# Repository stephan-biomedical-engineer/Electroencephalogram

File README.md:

# 🧠 Wearable EEG Device – Biomedical Instrumentation I

> A wearable EEG system for real-time brain activity monitoring, designed with embedded systems and IoT principles.

---

## 📚 Project Overview

This project presents a **wearable Electroencephalogram (EEG) device** developed for the **Biomedical Instrumentation I** course. It aims to acquire and process low-amplitude human brain signals (**5µV to 300µV**) across standard EEG frequency bands:

* **Delta (δ):** 0.5 – 4 Hz
* **Theta (θ):** 4 – 8 Hz
* **Alpha (α):** 8 – 13 Hz
* **Beta (β):** 13 – 30 Hz
* **Gamma (γ):** 30 – 100 Hz

This is a full-stack biomedical system, integrating **analog signal conditioning**, **high-resolution digital conversion**, and **wireless data transmission** for real-time EEG visualization.

<p align="center">
  
  <br>
  <b>EEG Hardware Prototype</b>
</p>

<p align="center">
  
  <br>
  <b>Real-Time EEG Interface in Qt</b>
</p>

<p align="center">
  
  <br>
  <b>Physical Setup</b>
</p>

---

## ⚙️ Hardware Architecture

### 🧩 Microcontroller Core

* **STM32H730VBT** SoC
* Features a **16-bit SAR ADC** up to **3.6 MSPS**, ideal for high-resolution EEG data acquisition.

### 🔌 Analog Front-End (AFE)

EEG signals are amplified \~**12000x** and filtered in a 3-stage analog pipeline:

1. **INA333 Instrumentation Amplifier** – 20x gain + initial passive filtering
2. **OPA333 Operational Amplifier** – 600x gain
3. **6th-Order Passive Bandpass Filter** – 0.5 Hz (HP) to 45 Hz (LP)

### 📡 Communication & Storage

* **External Flash:** W25Q512JV QSPI NOR Flash for firmware and logs
* **Wireless Co-Processor:** ESP32-C6-MINI-1H4, communicating via UART

---

## 💾 Firmware Architecture

### STM32H7 Side (Signal Acquisition)

* **DFSDM Peripheral** used for enhanced digital filtering
* **Oversampling & Bit Shifting** increase ADC ENOB
* Implements **Wavelet Transform** for real-time brain wave classification

### ESP32 Side (Wireless Stack)

* Developed using **ESP-IDF** and **FreeRTOS**
* Handles:

  * Serial communication with STM32
  * Data packetization
  * **Wi-Fi communication** to local host
  * **MQTT protocol** for lightweight IoT data streaming

---

## 🧪 Real-Time EEG Visualization

On the host side:

* A **Qt** interface provides live graphical feedback of EEG signals.
* Visualizes brain wave patterns and band activity in real time.

---

## 🛠️ Technologies Used

| Layer            | Tools & Components                         |
| ---------------- | ------------------------------------------ |
| Microcontroller  | STM32H730VBT, STM32CubeIDE                 |
| Analog Circuitry | INA333, OPA333, RC Filters                 |
| Wireless         | ESP32-C6, FreeRTOS (Not yet implemented)   | 
| Protocols        | UART, MQTT, Wi-Fi                          |
| Host Interface   | Qt, C++, HTML5, WebSocket/MQTT |

---

## 🚧 Future Improvements

* ✅ Integrate live FFT for spectral analysis
* ✅ Mobile dashboard version
* 🔲 Dry electrodes support
* 🔲 Artifact rejection (e.g., blink/motion noise)
* 🔲 Bluetooth Low Energy (BLE) alternative

---

## 👨‍🔬 Authors & Acknowledgments
Stephan Costa Barros - 
Electrical Engineering Department – Federal University of Uberlândia (UFU), Brazil

Marcelo Barros de Almeida - 
Electrical Engineering Department – Federal University of Uberlândia (UFU), Brazil

Alcimar Barbosa Soares - 
Electrical Engineering Department – Federal University of Uberlândia (UFU), Brazil

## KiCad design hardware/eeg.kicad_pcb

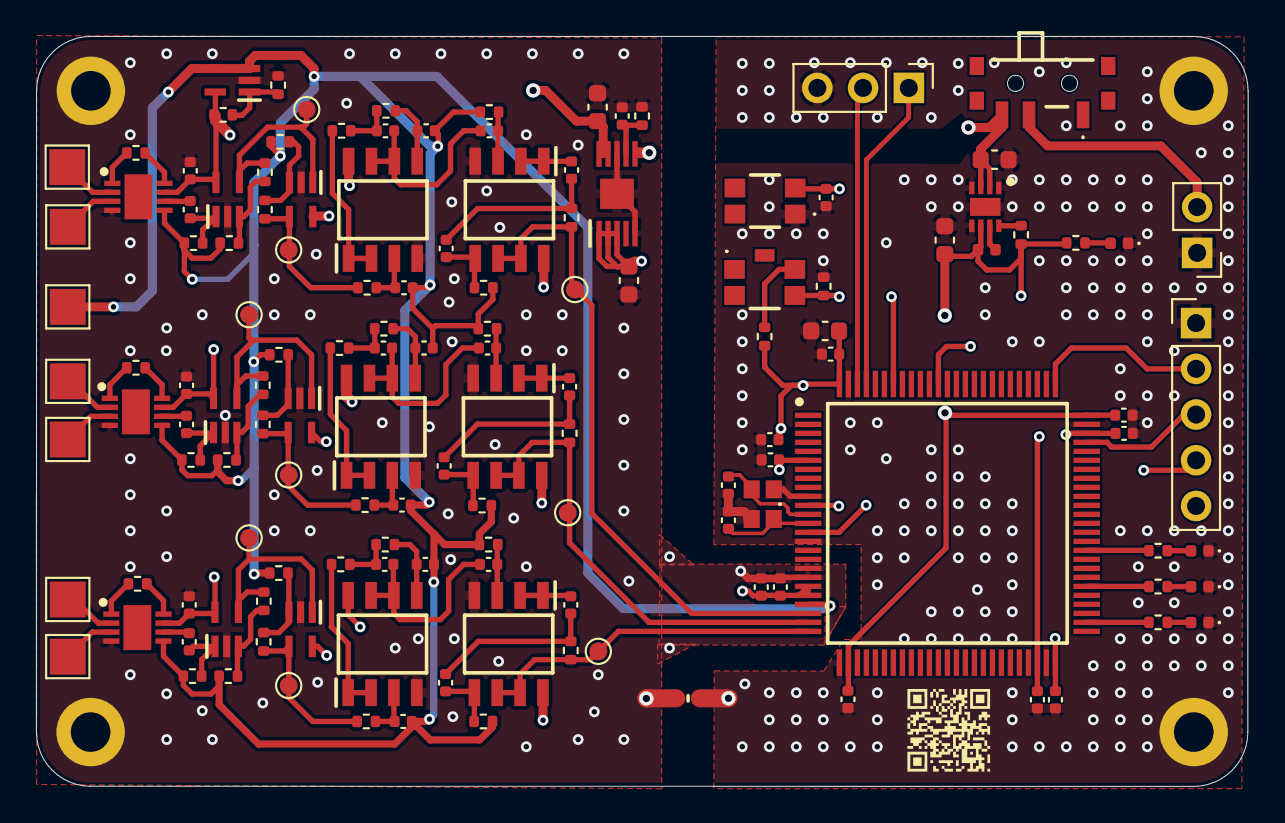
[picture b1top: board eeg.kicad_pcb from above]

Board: 4 copper layers, 67.3 x 41.7 mm, 141 parts (0 on the bottom side), 89 nets.

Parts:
C1, C9, C17, C39: 0.1uF; C_0402_1005Metric
C2, C10, C18: 330nF; C_0402_1005Metric
C3, C5, C11, C13, C19, C21: 36nF; C_0402_1005Metric
C4, C12, C20: 8.2nF; C_0402_1005Metric
C6, C7, C8, C14, C15, C16, C22, C23, C24: 300nF; C_0402_1005Metric
C25, C26, C27, C28, C29, C31, C35: 100nF; C_0402_1005Metric
C30, C40, C42: 4.7uF; C_0603_1608Metric
C32: 1uF; C_0402_1005Metric
C33, C34: 2.2uF; C_0402_1005Metric
C37, C38: 20pF; C_0402_1005Metric
C41: 0.47uF; C_0402_1005Metric
C43: 10uF; C_0603_1608Metric
C44: 22uF; C_0603_1608Metric
CH1+, CH1-, CH2+, CH2-, CH3+, CH3-: TestPoint; TestPoint_Pad_2.0x2.0mm
D1, D2, D3, D4: LED; LED_0402_1005Metric
FB1: FerriteBead_Small; BEADC1005X55N
H1, H2, H3, H4: MountingHole_Pad; MountingHole_2.2mm_M2_DIN965_Pad
IC1: TPS62162QDSGRQ1; SON50P200X200X80-9N
IC2: LT3042IMSE#PBF; SOP50P490X110-11N
IC3: STM32H730VBT6; QFP50P1600X1600X160-100N
IC4: OPA333AIDCKRG4; SOT65P210X110-5N
J1: Battery LiPO; PinHeader_1x02_P2.54mm_Vertical
J2: Conn_01x05; PinHeader_1x05_P2.54mm_Vertical
J4: Serial; PinHeader_1x03_P2.54mm_Vertical
L1: 2.2uH; L_0402_1005Metric
R1, R2: 1M; R_0402_1005Metric
R3, R15, R27: 2.04k; R_0402_1005Metric
R4, R16, R28: 910k; R_0402_1005Metric
R5, R7, R17, R19, R29, R31: 1.5k; R_0402_1005Metric
R6, R8, R18, R20, R30, R32: 750k; R_0402_1005Metric
R9, R21, R33: 97k; R_0402_1005Metric
R10, R22, R34: 149K; R_0402_1005Metric
R11, R23, R35: 276K; R_0402_1005Metric
R12, R24, R36: 967k; R_0402_1005Metric
R13, R25, R37: 1.93M; R_0402_1005Metric
R14, R26, R38: 484k; R_0402_1005Metric
R39, R40, R41, R42, R44: 1k; R_0402_1005Metric
R43: 10k; R_0402_1005Metric
R45: 33.2k; R_0402_1005Metric
R46: 100k; R_0402_1005Metric
REF: TestPoint; TestPoint_Pad_2.0x2.0mm
S1: PCM12SMTBR
SW2: SW_Push_Dual; TL1030AF160BQJ
SW3: SW_Push_Dual; TL1030AF350AQJ
TP1, TP2, TP3, TP4, TP5, TP6, TP7, TP8, TP9: TestPoint; TestPoint_Pad_D1.0mm
U1, U5, U9: INA333xxDRG; SON50P300X300X80-9N-D
U2, U6, U10, U17, U18, U19: OPA333xxDCK; SOT65P210X110-5N
U3, U4, U7, U8, U11, U12: MCP602; SOIC127P600X175-8N
Y1: Crystal_GND24_Small; 830107284409

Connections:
ADC_IN1: IC3.25 (PA3), R14.1, TP3.1, U4.6 (-), U4.7
ADC_IN2: IC3.24 (PA2), R26.1, TP6.1, U8.6 (-), U8.7
ADC_IN3: IC3.23 (PA1), R38.1, TP9.1, U12.6 (-), U12.7
BOOT: IC3.94 (BOOT0), R43.2, SW2.4
EEG_CH1+: CH1+.1, U1.3 (+)
EEG_CH1-: CH1-.1, U1.2 (-)
EEG_CH2+: CH2+.1, U5.3 (+)
EEG_CH2-: CH2-.1, U5.2 (-)
EEG_CH3+: CH3+.1, U9.3 (+)
EEG_CH3-: CH3-.1, U9.2 (-)
GND: C25.2, C26.2, C27.2, C28.2, C29.2, C30.2, C33.2, C34.2, C35.2, C37.2, C38.2, C39.2, C43.2, C44.2, D1.1 (K), D2.1 (K), D3.1 (K), D4.1 (K), FB1.1, H3.1, H4.1, IC1.1 (PGND), IC1.4 (AGND), IC1.5 (FB), IC1.9 (EP), IC3.10 (VSS_1), IC3.15 (PC0), IC3.26 (VSS_2), IC3.49 (VSS_3), IC3.74 (VSS_4), IC3.99 (VSS_5), J1.1, J2.1, J4.3, R43.1, SW3.1, Y1.2, Y1.4
GNDA: C1.1, C9.1, C17.1, C31.2, C32.2, C40.2, C41.2, C42.2, FB1.2, H1.1, H2.1, IC2.5 (ILIM), IC2.8 (GND_1), IC2.11 (GND_2), IC3.18 (PC3_C), IC3.19 (VSSA), IC4.2 (V-), R2.1, R45.2, U1.4 (V-), U2.2 (V-), U3.4 (V-), U4.4 (V-), U5.4 (V-), U6.2 (V-), U7.4 (V-), U8.4 (V-), U9.4 (V-), U10.2 (V-), U11.4 (V-), U12.4 (V-), U17.2 (V-), U18.2 (V-), U19.2 (V-)
HSE_I: C37.1, IC3.12 (PH0-OSC_IN), Y1.1
HSE_O: C38.1, IC3.13 (PH1-OSC_OUT), Y1.3
LED_1: IC3.60 (PD13), R39.1
LED_2: IC3.56 (PD9), R40.1
LED_3: IC3.52 (PB13), R41.1
MCU_RX: IC3.97 (PE0), J4.1
MCU_TX: IC3.98 (PE1), J4.2
unnamed: C2.1, U1.6
unnamed: C5.1, R10.1, R11.1
unnamed: C7.1, C8.2, R14.2
unnamed: C10.1, U5.6
unnamed: C13.1, R22.1, R23.1
unnamed: C15.1, C16.2, R26.2
unnamed: C18.1, U9.6
unnamed: C21.1, R34.1, R35.1
unnamed: C23.1, C24.2, R38.2
unnamed: D1.2 (A), R44.2
unnamed: D2.2 (A), R39.2
unnamed: D3.2 (A), R40.2
unnamed: D4.2 (A), R41.2
unnamed: IC1.8 (PG), R46.1
unnamed: IC1.7 (SW), L1.1
unnamed: C41.1, IC2.7 (SET), R45.1
unnamed: IC4.1 (+IN), R1.1, R2.2
unnamed: R3.1, U1.8 (Rg)
unnamed: R3.2, U1.1 (Rg)
unnamed: R8.2, R9.1, TP2.1, U17.4
unnamed: R15.1, U5.8 (Rg)
unnamed: R15.2, U5.1 (Rg)
unnamed: R20.2, R21.1, TP5.1, U18.4
unnamed: R27.1, U9.8 (Rg)
unnamed: R27.2, U9.1 (Rg)
unnamed: R32.2, R33.1, TP8.1, U19.4
unnamed: R42.1, SW2.2
unnamed: C2.2, R4.1, U2.1 (+)
unnamed: R5.1, R6.1, U2.3 (-)
unnamed: C3.1, R9.2, U3.3 (+)
unnamed: R10.2, U3.1, U3.2 (-)
unnamed: C4.1, R11.2, U3.5 (+)
unnamed: C5.2, C6.2, U3.6 (-), U3.7
unnamed: C6.1, R12.2, U4.3 (+)
unnamed: C7.2, U4.1, U4.2 (-)
unnamed: C8.1, R13.2, U4.5 (+)
unnamed: C10.2, R16.1, U6.1 (+)
unnamed: R17.1, R18.1, U6.3 (-)
unnamed: C11.1, R21.2, U7.3 (+)
unnamed: R22.2, U7.1, U7.2 (-)
unnamed: C12.1, R23.2, U7.5 (+)
unnamed: C13.2, C14.2, U7.6 (-), U7.7
unnamed: C14.1, R24.2, U8.3 (+)
unnamed: C15.2, U8.1, U8.2 (-)
unnamed: C16.1, R25.2, U8.5 (+)
unnamed: C18.2, R28.1, U10.1 (+)
unnamed: R29.1, R30.1, U10.3 (-)
unnamed: C19.1, R33.2, U11.3 (+)
unnamed: R34.2, U11.1, U11.2 (-)
unnamed: C20.1, R35.2, U11.5 (+)
unnamed: C21.2, C22.2, U11.6 (-), U11.7
unnamed: C22.1, R36.2, U12.3 (+)
unnamed: C23.2, U12.1, U12.2 (-)
unnamed: C24.1, R37.2, U12.5 (+)
unnamed: R6.2, TP1.1, U2.4, U17.1 (+)
unnamed: R7.1, R8.1, U17.3 (-)
unnamed: R18.2, TP4.1, U6.4, U18.1 (+)
unnamed: R19.1, R20.1, U18.3 (-)
unnamed: R30.2, TP7.1, U10.4, U19.1 (+)
unnamed: R31.1, R32.1, U19.3 (-)
RESET: C39.1, IC3.14 (NRST), SW3.2
SWCLK: IC3.76 (PA14), J2.2
SWDIO: IC3.72 (PA13), J2.3
SWO: IC3.89 (PB3), J2.4
VCAP: C33.1, C34.1, IC3.48 (VCAP_1), IC3.73 (VCAP_2)
VDD33: C25.1, C26.1, C27.1, C28.1, C29.1, C30.1, C35.1, C44.1, IC1.6 (VOS), IC3.6 (VBAT), IC3.11 (VDD_1), IC3.27 (VDD_2), IC3.50 (VDD_3), IC3.75 (VDD_4), IC3.100 (VDD_5), J2.5, L1.2, R42.2, R44.1, R46.2
VDDA33: C1.2, C9.2, C17.2, C31.1, C32.1, C42.1, IC2.9 (OUTS), IC2.10 (OUT), IC3.20 (VREF+), IC3.21 (VDDA), IC4.5 (V+), R1.2, U1.7 (V+), U2.5 (V+), U3.8 (V+), U4.8 (V+), U5.7 (V+), U6.5 (V+), U7.8 (V+), U8.8 (V+), U9.7 (V+), U10.5 (V+), U11.8 (V+), U12.8 (V+), U17.5 (V+), U18.5 (V+), U19.5 (V+)
VIN_BAT: C40.1, C43.1, IC1.2 (VIN), IC1.3 (EN), IC2.1 (IN_1), IC2.2 (IN_2), IC2.3 (EN/UV), IC2.6 (PGFB), S1.3 (NO)
VIN_SWT: J1.2, S1.2 (COM)
VREF: C3.2, C4.2, C11.2, C12.2, C19.2, C20.2, IC3.22 (PA0), IC4.3 (-IN), IC4.4 (OUT), R4.2, R5.2, R7.2, R12.1, R13.1, R16.2, R17.2, R19.2, R24.1, R25.1, R28.2, R29.2, R31.2, R36.1, R37.1, REF.1, U1.5 (Ref), U5.5 (Ref), U9.5 (Ref)

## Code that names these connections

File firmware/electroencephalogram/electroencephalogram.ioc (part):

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Mcu.Name=STM32H730VBTx
Mcu.Package=LQFP100
Mcu.UserName=STM32H730VBTx
PA0.Mode=IN16-Single-Ended
PA0.Signal=ADC1_INP16
PA1.Mode=IN17-Single-Ended
PA1.Signal=ADC1_INP17
PA13(JTMS/SWDIO).Mode=Trace_Asynchronous_SW
PA13(JTMS/SWDIO).Signal=DEBUG_JTMS-SWDIO
PA14(JTCK/SWCLK).Mode=Trace_Asynchronous_SW
PA14(JTCK/SWCLK).Signal=DEBUG_JTCK-SWCLK
PA2.Signal=ADCx_INP14
PA3.Signal=ADCx_INP15
PA6.Signal=OCTOSPIM_P1_IO3
PA7.Signal=OCTOSPIM_P1_IO2
PB1.Signal=OCTOSPIM_P1_IO0
PB13.Signal=GPIO_Output
PB2.Signal=OCTOSPIM_P1_CLK
PB3(JTDO/TRACESWO).Mode=Trace_Asynchronous_SW
PB3(JTDO/TRACESWO).Signal=DEBUG_JTDO-SWO
PD13.Signal=GPIO_Output
PD9.Signal=GPIO_Output
PE0.Mode=Asynchronous
PE0.Signal=UART8_RX
PE1.Mode=Asynchronous
PE1.Signal=UART8_TX
PE7.GPIOParameters=GPIO_Label
PE7.GPIO_Label=RESET_FLASH
PE7.Signal=GPIO_Output
PH0-OSC_IN.Mode=HSE-External-Oscillator
PH0-OSC_IN.Signal=RCC_OSC_IN
PH1-OSC_OUT.Mode=HSE-External-Oscillator
PH1-OSC_OUT.Signal=RCC_OSC_OUT
RCC.HSE_VALUE=30000000
RCC.SYSCLKFreq_VALUE=30000000
RCC.SYSCLKSource=RCC_SYSCLKSOURCE_HSE
board=custom

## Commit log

2025-06-22 EEG first commit
2025-06-22 .gitignore exceptions
2025-06-22 KiCAD libraries includes
2025-06-22 README
2025-07-06 firmware ESP32
2025-07-06 Revert "README"
    This reverts commit 0629bfb1291f558bdffaff377363a884e0051eaa.
2025-07-06 Firmware LED ESP32
2025-08-04 hardware final update
2025-08-08 Final Hardware Implementation
2025-08-18 CRC+COBS+UART+ADC+CBF implementation
2025-08-18 Interface Real-Time Plotting
2025-09-03 Firmware corrections
2025-09-06 UART DMA inclusion
2025-09-09 Firmware update, 4 division by channels in interface, hardware update
2025-09-12 Interface com FFT
2025-09-13 ADC Calibration Stage
2025-09-13 Hardware att
2025-09-18 Real Time inteface validated
2025-09-21 Real Time interface final
2025-09-21 Final Firmware validated
2025-09-21 Hardware v1 final version
2025-09-21 Removing dummy files
2025-09-21 Revise README with updated hardware and firmware details
    Updated hardware specifications and improved analog signal amplification details.
2025-09-21 Fix formatting issues in README.md
2025-09-21 Update README.md with project details
2025-09-21 Adding images
2025-09-28 Update README with project details and structure
